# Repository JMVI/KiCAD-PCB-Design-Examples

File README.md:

# KiCAD-PCB-Design-Examples
PCB design examples using KiCAD 8

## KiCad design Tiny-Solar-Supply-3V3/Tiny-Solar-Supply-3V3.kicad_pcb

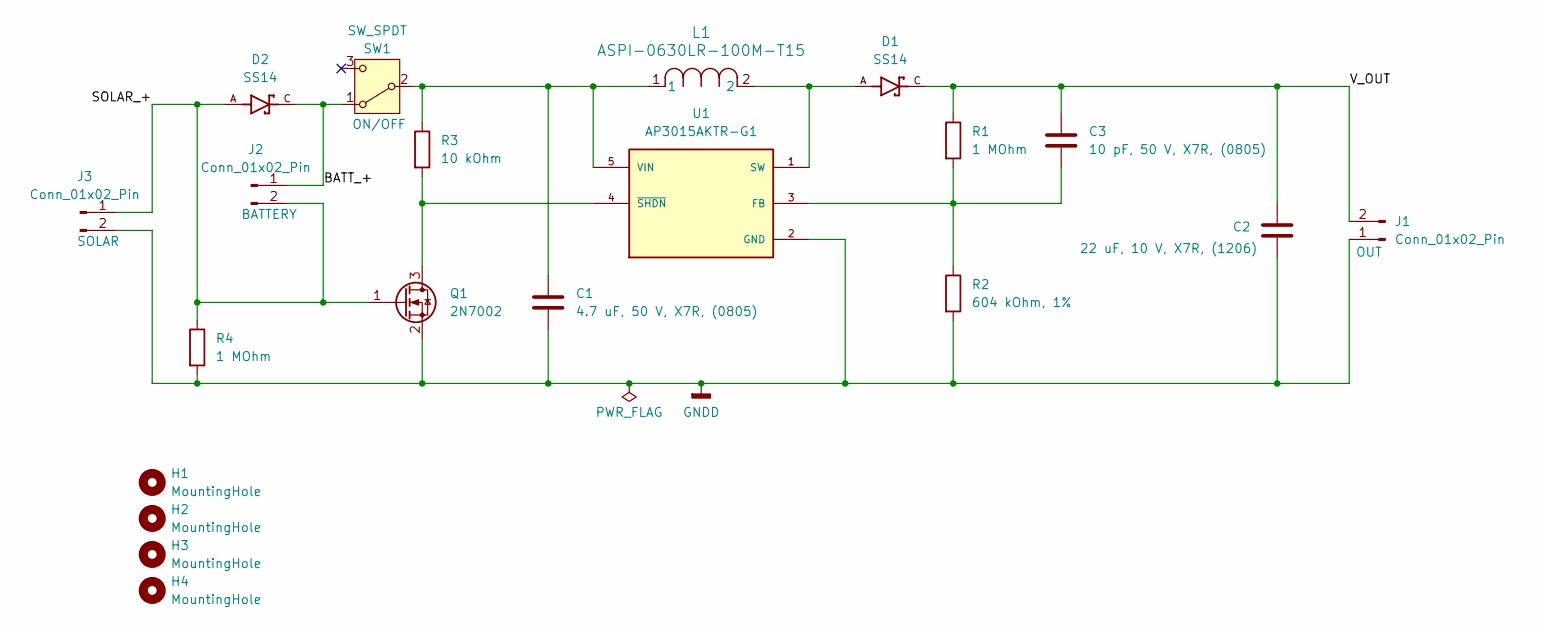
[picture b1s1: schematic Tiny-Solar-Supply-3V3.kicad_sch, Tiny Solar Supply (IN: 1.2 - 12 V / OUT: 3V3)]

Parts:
C1: 4.7 uF, 50 V, X7R, (0805); C_0805_2012Metric
C2: 22 uF, 10 V, X7R, (1206); C_1206_3216Metric
C3: 10 pF, 50 V, X7R, (0805); C_0805_2012Metric
D1, D2: SS14; DIOM4325X250N; PARTREV O2102
H1, H2, H3, H4: MountingHole; MountingHole_1.8mm
J1, J2, J3: Conn_01x02_Pin; PinHeader_1x02_P2.54mm_Vertical
L1: ASPI-0630LR-100M-T15; IND_ASPI-0630LR_ABR
Q1: 2N7002; SOT-23
R1, R4: 1 MOhm; R_0805_2012Metric
R2: 604 kOhm, 1%; R_0805_2012Metric
R3: 10 kOhm; R_0805_2012Metric
SW1: SW_SPDT; SW_Slide_SPDT_Straight_CK_OS102011MS2Q
U1: AP3015AKTR-G1; SOT95P280X145-5N; PARTREV 1.4

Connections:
/BATT_+: D2.C, J2.1, SW1.1 (A)
/SOLAR_+: D2.A, J2.2, J3.1, Q1.1 (G), R4.1
/V_OUT: C2.1, C3.1, D1.C, J1.2, R1.1
GNDD: C1.2, C2.2, J1.1, J3.2, Q1.2 (S), R2.2, R4.2, U1.2 (GND)
unnamed: Q1.3 (D), R3.2, U1.4 (~SHDN)
unnamed: C1.1, L1.1, R3.1, SW1.2 (B), U1.5 (VIN)
unnamed: C3.2, R1.2, R2.1, U1.3 (FB)
unnamed: D1.A, L1.2, U1.1 (SW)

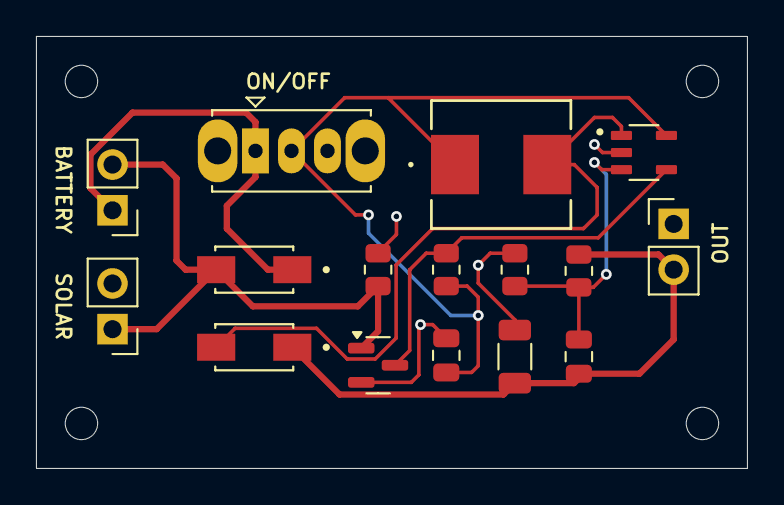
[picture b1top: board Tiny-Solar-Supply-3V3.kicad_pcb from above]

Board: 2 copper layers, 39.5 x 24.0 mm, 20 parts (0 on the bottom side), 8 nets.

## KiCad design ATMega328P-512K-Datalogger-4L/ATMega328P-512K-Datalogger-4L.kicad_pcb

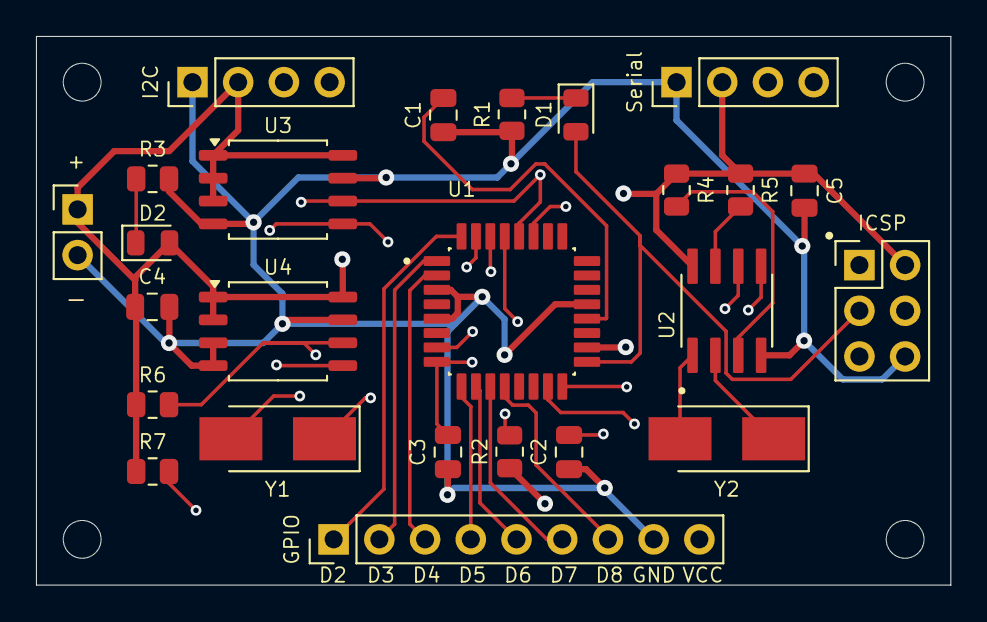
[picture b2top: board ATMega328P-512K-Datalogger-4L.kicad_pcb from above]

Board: 4 copper layers, 50.8 x 30.5 mm, 29 parts (0 on the bottom side), 26 nets.

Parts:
BT1: Battery; PinHeader_1x02_P2.54mm_Vertical
C1, C5: 0.1u; C_0805_2012Metric
C2, C3: 22p; C_0805_2012Metric
C4: 100n; C_0805_2012Metric
D1, D2: LED; LED_0805_2012Metric
GPIO: Conn_01x09_Pin; PinHeader_1x09_P2.54mm_Vertical
H1, H2, H3, H4: MountingHole; MountingHole_2.1mm
I2C: Conn_01x04_Pin; PinHeader_1x04_P2.54mm_Vertical
ICSP: Conn_02x03_Odd_Even; PinHeader_2x03_P2.54mm_Vertical
R1, R3: 330; R_0805_2012Metric
R2, R4, R5: 10K; R_0805_2012Metric
R6, R7: 4.7K; R_0805_2012Metric
Serial: Conn_01x04_Pin; PinHeader_1x04_P2.54mm_Vertical
U1: ATMEGA328P-AU; QFP80P900X900X120-32N
U2: DS1337S_; SOIC127P600X175-8N
U3, U4: 24LC1025; SOIC-8_5.23x5.23mm_P1.27mm
Y1: 16 MHz; Crystal_SMD_5032-2Pin_5.0x3.2mm_HandSoldering
Y2: 32.768 KHz; Crystal_SMD_5032-2Pin_5.0x3.2mm_HandSoldering

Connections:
/D2: GPIO.1, U1.32 (PD2)
/D3: GPIO.2, U1.1 (PD3)
/D4: GPIO.3, U1.2 (PD4)
/D5: GPIO.4, U1.9 (PD5)
/D6: GPIO.5, U1.10 (PD6)
/D7: GPIO.6, U1.11 (PD7)
/D8: GPIO.7, U1.12 (PB0)
/MISO: ICSP.1, U1.16 (PB4)
/MOSI: ICSP.4, U1.15 (PB3)
/RESET: ICSP.5, R2.2, U1.29 (PC6/~RESET)
/RX: Serial.4, U1.30 (PD0)
/SCK: D1.2 (A), ICSP.3, U1.17 (PB5)
/SCL: I2C.4, R6.2, U1.28 (PC5), U2.6 (SCL), U3.6 (SCL), U4.6 (SCL)
/SDA: I2C.3, R7.2, U1.27 (PC4), U2.5 (SDA), U3.5 (SDA), U4.5 (SDA)
/TX: Serial.3, U1.31 (PD1)
/VCC: BT1.1 (+), C4.1, C5.1, D2.2 (A), GPIO.9, I2C.2, ICSP.2, R2.1, R4.1, R5.1, R6.1, R7.1, Serial.2, U1.18 (AVCC), U2.8 (VCC), U3.1 (A0), U3.2 (A1), U3.3 (A2), U3.8 (VCC), U4.1 (A0), U4.2 (A1), U4.8 (VCC)
GND: BT1.2 (-), C1.1, C2.1, C3.1, C4.2, C5.2, GPIO.8, I2C.1, ICSP.6, R1.1, R3.2, Serial.1, U1.3 (GND), U1.5 (GND), U1.21 (GND), U2.4 (GND), U3.4 (GND), U3.7 (WP), U4.3 (A2), U4.4 (GND), U4.7 (WP)
unnamed: D1.1 (K), R1.2
unnamed: D2.1 (K), R3.1
unnamed: C1.2, U1.20 (AREF)
unnamed: C2.2, U1.7 (PB6), Y1.2
unnamed: C3.2, U1.8 (PB7), Y1.1
unnamed: R5.2, U2.7 (SQW/~INT)
unnamed: U2.1 (X1), Y2.2
unnamed: U2.2 (X2), Y2.1
unnamed: R4.2, U2.3 (~INTA)

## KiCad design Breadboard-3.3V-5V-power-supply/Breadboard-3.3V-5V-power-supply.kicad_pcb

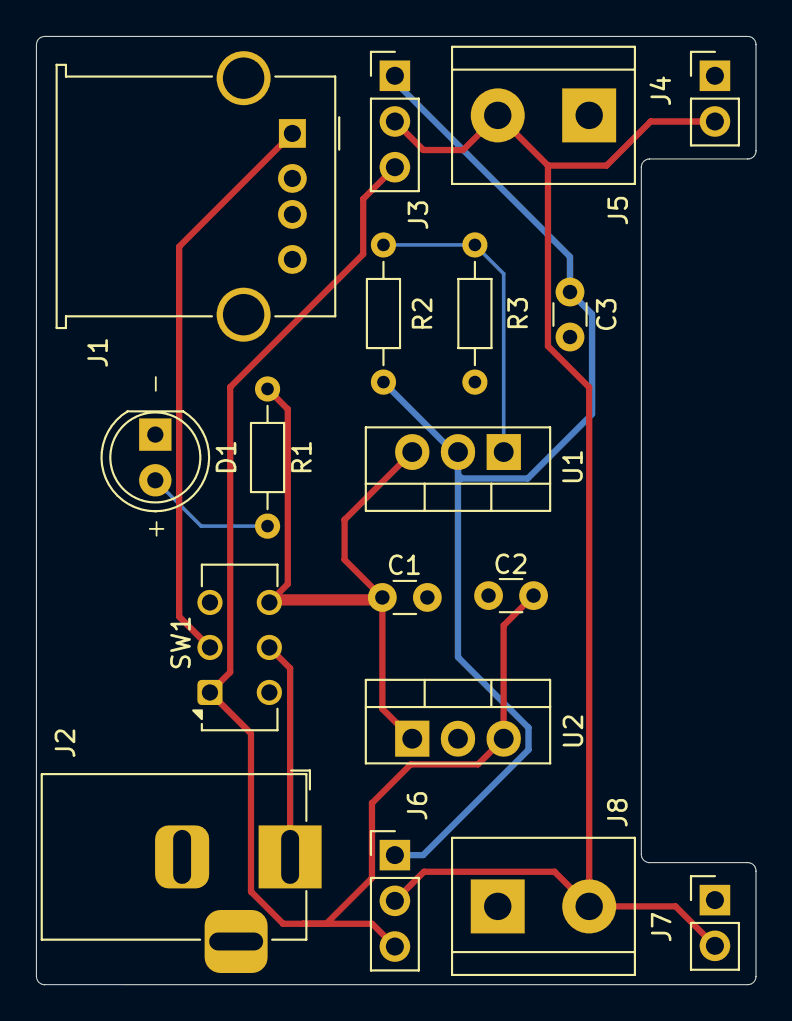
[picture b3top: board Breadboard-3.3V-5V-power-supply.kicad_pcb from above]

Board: 2 copper layers, 40.0 x 52.7 mm, 18 parts (0 on the bottom side), 9 nets.

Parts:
C1: 10u; C_Disc_D3.0mm_W1.6mm_P2.50mm
C2: 0.1u; C_Disc_D3.0mm_W1.6mm_P2.50mm
C3: 1u; C_Disc_D3.0mm_W1.6mm_P2.50mm
D1: LED; LED_D5.0mm
J1: USB_A; USB_A_Molex_67643_Horizontal
J2: Barrel_Jack_Switch; BarrelJack_Horizontal
J3, J6: Conn_01x03_Pin; PinHeader_1x03_P2.54mm_Vertical
J4, J7: Conn_01x02_Pin; PinHeader_1x02_P2.54mm_Vertical
J5, J8: Screw_Terminal_01x02; TerminalBlock_bornier-2_P5.08mm
R1, R2: 330; R_Axial_DIN0204_L3.6mm_D1.6mm_P7.62mm_Horizontal
R3: 560; R_Axial_DIN0204_L3.6mm_D1.6mm_P7.62mm_Horizontal
SW1: SW_DPDT_x2; SW_CK_JS202011CQN_DPDT_Straight
U1: LM317_TO-220; TO-220-3_Vertical
U2: LM7805_TO220; TO-220-3_Vertical

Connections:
/3.3V: C3.1, J3.1, J6.1, R2.1, U1.2 (VO)
/5V: C2.1, J3.3, J6.3, SW1.1 (A), U2.3 (VO)
/12V: C1.1, R1.1, SW1.4 (A), U1.3 (VI), U2.1 (VI)
/PWR_IN: J2.1, SW1.5 (B)
/PWR_OUT: J3.2, J4.2, J5.2, J6.2, J7.2, J8.2
/USB_IN: J1.1 (VBUS), SW1.2 (B)
GND: C1.2, C2.2, C3.2, D1.1 (K), J1.4 (GND), J2.2, J2.3, J4.1, J5.1, J7.1, J8.1, R3.2, U2.2 (GND)
unnamed: D1.2 (A), R1.2
unnamed: R2.2, R3.1, U1.1 (ADJ)

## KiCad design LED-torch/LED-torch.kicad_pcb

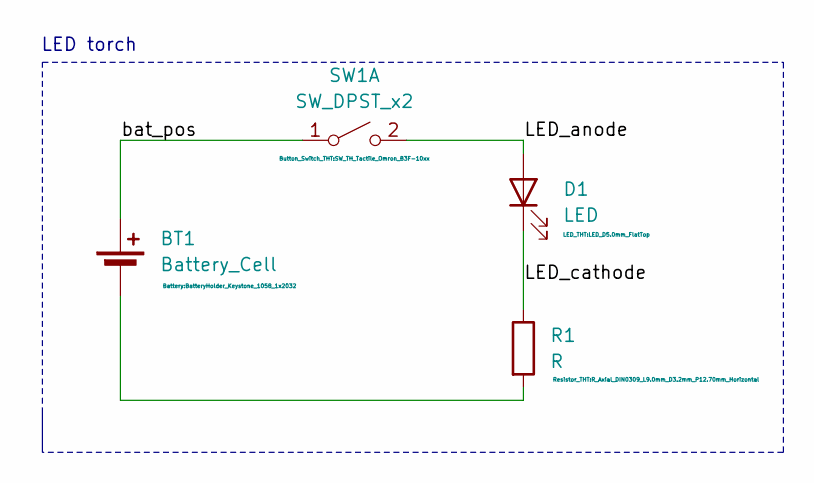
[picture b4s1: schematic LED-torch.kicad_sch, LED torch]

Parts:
BT1: Battery_Cell; BatteryHolder_Keystone_1058_1x2032
D1: LED; LED_D5.0mm_FlatTop
R1: R; R_Axial_DIN0309_L9.0mm_D3.2mm_P12.70mm_Horizontal
SW1: SW_DPST_x2; SW_TH_Tactile_Omron_B3F-10xx

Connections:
/LED_anode: D1.2 (A), SW1.2 (B)
/LED_cathode: D1.1 (K), R1.1
/bat_pos: BT1.1 (+), SW1.1 (A)
unnamed: BT1.2 (-), R1.2

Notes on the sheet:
LED torch

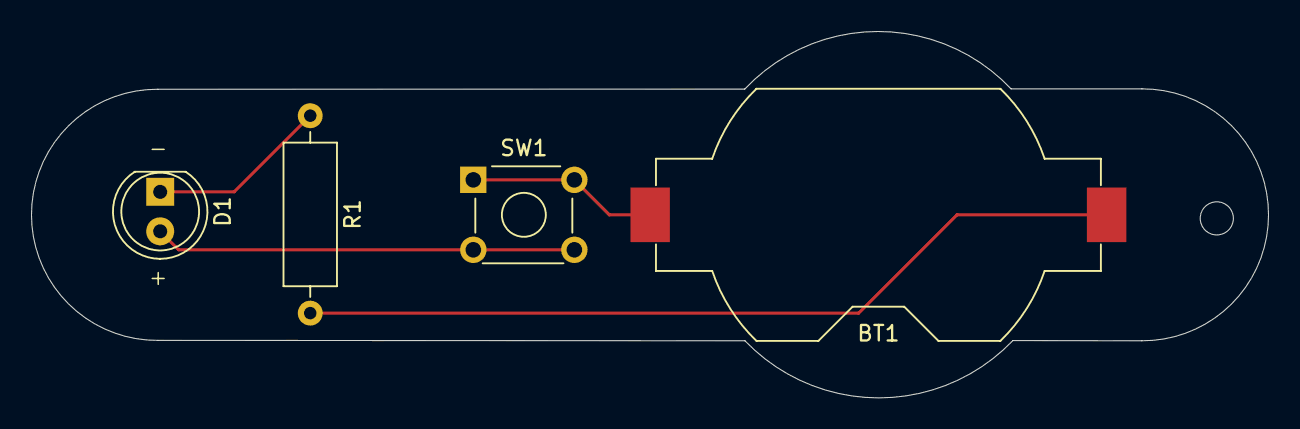
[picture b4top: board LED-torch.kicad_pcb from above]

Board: 2 copper layers, 79.6 x 23.6 mm, 4 parts (0 on the bottom side), 4 nets.

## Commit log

2025-01-06 [LED TORCH][v1.0.0]
    ### ADD
    - LED torch files are added.
2025-01-06 [BREADBOARD-3.3V-5V-POWER-SUPPLY][v1.0.0]
    ### ADD
    - Power supply schematics is added.
2025-01-12 [BREADBOARD-3.3V-5V-POWER-SUPPLY][v1.0.0]
    ### UPDATE
    - PCB layout first outline and component placement.
    - USB A connector is added to schematic (not to layout).
2025-01-23 [BREADBOARD-3.3V-5V-POWER-SUPPLY][v1.0.0]
    ### ADD
    - Gerber files are created.
    ### UPDATE
    - PCB layout routing is completed.
    ### FIX
    - Output power net labels are fixed.
2025-01-23 [BREADBOARD-3.3V-5V-POWER-SUPPLY][v1.0.0]
    ### FIX
    - Top screw terminal block orientation is fixed.
    ### UPDATE
    - Screw terminals 3D model are added.
    - Output jumpers 3D model orientation are fixed.
    - Gerber files are updated.
2025-01-23 [BREADBOARD-3.3V-5V-POWER-SUPPLY][v1.0.0]
    ### FIX
    - Top screw terminal block silkscreen is fixed.
2025-01-28 [ATMEGA328P-DATALOGGER][v1.0.0]
    ### ADD
    - MCU datalogger project is created.
    - Schematics components placement.
2025-01-30 [ATMEGA328P-DATALOGGER][v1.0.0]
    ### ADD
    - ATMega328P-AU and DS1337S footprints are added to project.
    ### UPDATE
    - Footprints have been associated.
2025-01-30 [ATMEGA328P-DATALOGGER][v1.0.0]
    ### UPDATE
    - Schematics components wiring.
2025-01-30 [ATMEGA328P-DATALOGGER][v1.0.0]
    ### UPDATE
    - Schematics connectors wiring.
    - Comments and annotations.
2025-02-02 [ATMEGA328P-DATALOGGER][v1.0.0]
    ### UPDATE
    - Project is renamed for 2-Layer PCB version.
    - PCB footprint placement and routing.
2025-02-02 [ATMEGA328P-DATALOGGER][v1.0.0]
    ### UPDATE
    - PCB silkscreen.
2025-02-04 [ATMEGA328P-DATALOGGER][v1.0.0]
    ### FIX
    - SCK and SCL pin short-circuit is fixed.
2025-02-04 [ATMEGA328P-DATALOGGER][v1.0.0]
    ### ADD
    - Gerber files are generated.
    ### FIX
    - PCB layout fixes of SCL and SCK pins.
    - Missing 3D models are added.
2025-02-05 [ATMEGA328P-DATALOGGER][v1.0.0]
    ### ADD
    - Gerber files for 4-layer PCB version are generated.
    ### UPDATE
    - 4-layer PCB layout routing and filling.
    - ERC and DRC completed.
2025-02-06 [ATMEGA328P-DATALOGGER][v1.0.0]
    ### ADD
    - JMVI logo footprint added.
2025-07-16 [TINY-SOLAR-SUPPLY-3V3][v1.0.0]
    ### ADD
    - Tiny solar power supply project is created (schematics, PCB layout, and Gerber files).
